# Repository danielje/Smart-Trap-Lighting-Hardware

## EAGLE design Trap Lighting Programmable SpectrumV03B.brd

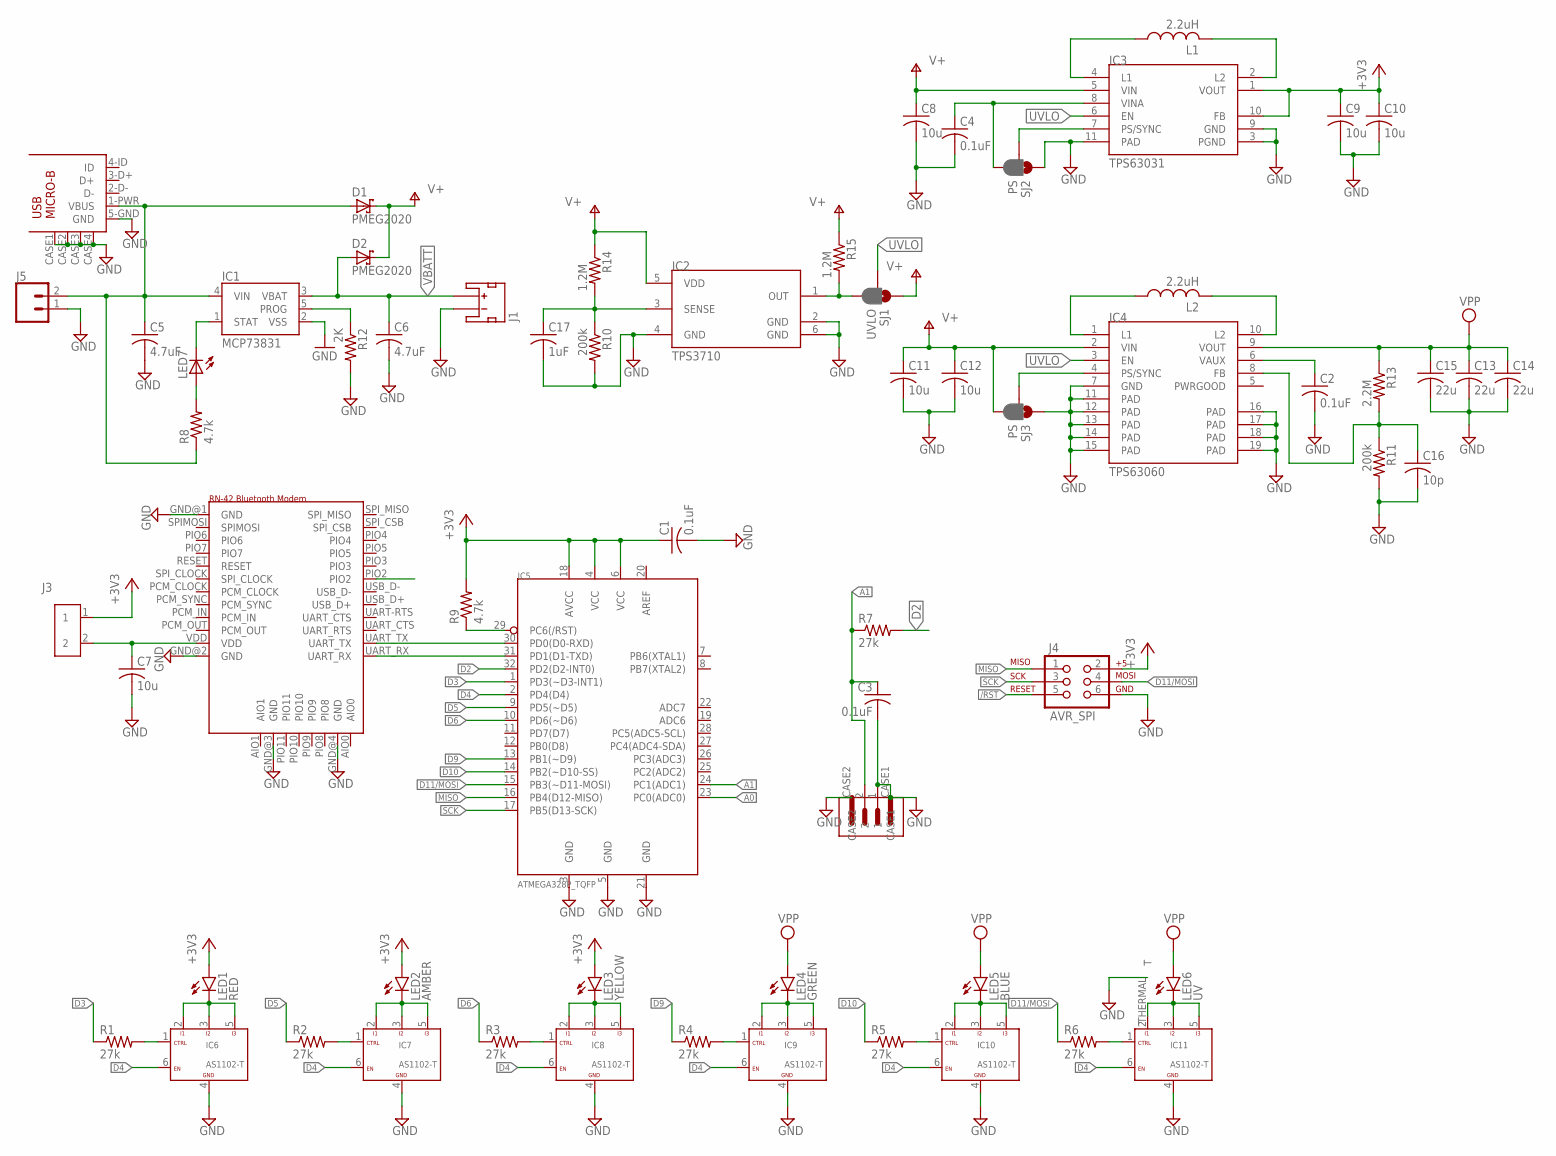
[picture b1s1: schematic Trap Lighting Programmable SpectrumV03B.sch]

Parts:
A1: RN-42_BLUETOOTH; RN-42
C1, C2, C3, C4: 0.1uF; C0805
C5, C6: 4.7uF; C0805
C7, C8, C9, C10, C11, C12: 10u; C0805
C13, C14, C15: 22u; C1206
C16: 10p; C0805
C17: 1uF; C0805
D1, D2: PMEG2020; SOD323_ST
IC1: MCP73831; SOT23-5
IC2: TPS3710; SOT6
IC3: TPS63031; VSON-10
IC4: TPS63060; WSON1-10
IC5: ATMEGA328P_TQFP; TQFP-32
IC6, IC7, IC8, IC9, IC10, IC11: AS1102-T; SC70-6
J1: JST_2MM_MALE; JST-2-SMD
J2: 2PIN_SMD_PHOENIX_CONTACTVERTICAL_PACKAGE; 2-PIN-VERT-PHOENIX_SMD
J3: 2MM_SMD_M_HEADER; 2MM_MALE_SMD_HEADER
J4: AVR_SPI; 2X3
J5: CONN_02PTH3; 1X02_LONGPADS
L1, L2: 2.2uH; VLF302512MT-2R2M-CA_INDUCTOR
LED1: RED; LED_TT_OVS5MX
LED2: AMBER; LED_TT_OVS5MX
LED3: YELLOW; LED_TT_OVS5MX
LED4: GREEN; LED_LUXEON_3535L
LED5: BLUE; LED_TT_OVS5MX
LED6: UV; LED_LITEON_CO3_UV
LED7: LEDCHIPLED_0805; CHIPLED_0805
R1, R2, R3, R4, R5, R6, R7: 27k; R0805
R8, R9: 4.7k; R0805
R10, R11: 200k; R0805
R12: 2K; R0805
R13: 2.2M; R0805
R14, R15: 1.2M; R0805
SJ1: UVLO; SMT-JUMPER_3_1-NC_PASTE_SILK
SJ2, SJ3: PS; SMT-JUMPER_3_1-NC_PASTE_SILK
USB1: USB-MICRO-B; USB_MICRO_B_WURTH_629105136821

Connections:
3.3V: C1.1, C9.1, C10.1, IC3.1 (VOUT), IC3.10 (FB), IC5.4 (VCC), IC5.6 (VCC), IC5.18 (AVCC), J3.1, J4.2, LED1.A, LED2.A, LED3.A, R9.2
/RST: IC5.29 (PC6(/RST)), J4.5, R9.1
A0: IC5.23 (PC0(ADC0))
A1: C3.1, IC5.24 (PC1(ADC1)), J2.2, R7.1
BT_CONNECT: A1.PIO2
D2: IC5.32 (PD2(D2-INT0)), R7.2
D3: IC5.1 (PD3(~D3-INT1)), R1.1
D4: IC5.2 (PD4(D4)), IC6.6 (EN), IC7.6 (EN), IC8.6 (EN), IC9.6 (EN), IC10.6 (EN), IC11.6 (EN)
D5: IC5.9 (PD5(~D5)), R2.1
D6: IC5.10 (PD6(~D6)), R3.1
D9: IC5.13 (PB1(~D9)), R4.1
D10: IC5.14 (PB2(~D10-SS)), R5.1
D11/MOSI: IC5.15 (PB3(~D11-MOSI)), J4.4, R6.1
GND: A1.GND@1 (GND), A1.GND@2 (GND), A1.GND@3 (GND), A1.GND@4 (GND), C1.2, C2.2, C3.2, C4.2, C5.2, C6.2, C7.2, C8.2, C9.2, C10.2, C11.2, C12.2, C13.2, C14.2, C15.2, C16.2, C17.2, IC1.2 (VSS), IC2.2 (GND), IC2.4 (GND), IC2.6 (GND), IC3.3 (PGND), IC3.9 (GND), IC3.11 (PAD), IC4.7 (GND), IC4.11 (PAD), IC4.12 (PAD), IC4.13 (PAD), IC4.14 (PAD), IC4.15 (PAD), IC4.16 (PAD), IC4.17 (PAD), IC4.18 (PAD), IC4.19 (PAD), IC5.3 (GND), IC5.5 (GND), IC5.21 (GND), IC6.4 (GND), IC7.4 (GND), IC8.4 (GND), IC9.4 (GND), IC10.4 (GND), IC11.4 (GND), J1.1 (-), J2.1, J2.CASE1, J2.CASE2, J4.6, J5.1, LED6.THERMAL (T), R10.2, R11.2, R12.2, SJ2.1, SJ3.1, USB1.5-GND (GND), USB1.CASE1 (CASE), USB1.CASE2 (CASE), USB1.CASE3 (CASE), USB1.CASE4 (CASE)
MCURX: A1.UART_TX, IC5.30 (PD0(D0-RXD))
MCUTX: A1.UART_RX, IC5.31 (PD1(D1-TXD))
MISO: IC5.16 (PB4(D12-MISO)), J4.1
unnamed: IC1.1 (STAT), LED7.C
unnamed: IC8.1 (CTRL), R3.2
unnamed: IC9.1 (CTRL), R4.2
unnamed: IC2.1 (OUT), R15.2, SJ1.3
unnamed: A1.VDD, C7.1, J3.2
unnamed: IC10.1 (CTRL), R5.2
unnamed: IC11.1 (CTRL), R6.2
unnamed: IC7.1 (CTRL), R2.2
unnamed: LED7.A, R8.2
unnamed: IC1.5 (PROG), R12.1
unnamed: C17.1, IC2.3 (SENSE), R10.1, R14.2
unnamed: IC3.2 (L2), L1.2
unnamed: IC3.4 (L1), L1.1
unnamed: IC3.7 (PS/SYNC), SJ2.2
unnamed: IC8.2 (I1), IC8.3 (I2), IC8.5 (I3), LED3.C
unnamed: IC9.2 (I1), IC9.3 (I2), IC9.5 (I3), LED4.C
unnamed: IC10.2 (I1), IC10.3 (I2), IC10.5 (I3), LED5.C
unnamed: IC11.2 (I1), IC11.3 (I2), IC11.5 (I3), LED6.K (C)
unnamed: IC7.2 (I1), IC7.3 (I2), IC7.5 (I3), LED2.C
unnamed: IC6.1 (CTRL), R1.2
unnamed: C4.1, IC3.8 (VINA), SJ2.3
unnamed: IC6.2 (I1), IC6.3 (I2), IC6.5 (I3), LED1.C
unnamed: IC4.4 (PS/SYNC), SJ3.2
unnamed: IC4.1 (L1), L2.1
unnamed: IC4.10 (L2), L2.2
unnamed: C2.1, IC4.6 (VAUX)
unnamed: C16.1, IC4.8 (FB), R11.1, R13.2
SCK: IC5.17 (PB5(D13-SCK)), J4.3
USB_VIN: C5.1, D1.A, IC1.4 (VIN), J5.2, R8.1, USB1.1-PWR (VBUS)
UVLO: IC3.6 (EN), IC4.3 (EN), SJ1.2
V+: C8.1, C11.1, C12.1, D1.C, D2.C, IC2.5 (VDD), IC3.5 (VIN), IC4.2 (VIN), R14.1, R15.1, SJ1.1, SJ3.3
VBATT: C6.1, D2.A, IC1.3 (VBAT), J1.2 (+)
VPP: C13.1, C14.1, C15.1, IC4.9 (VOUT), LED4.A, LED5.A, LED6.A, R13.1

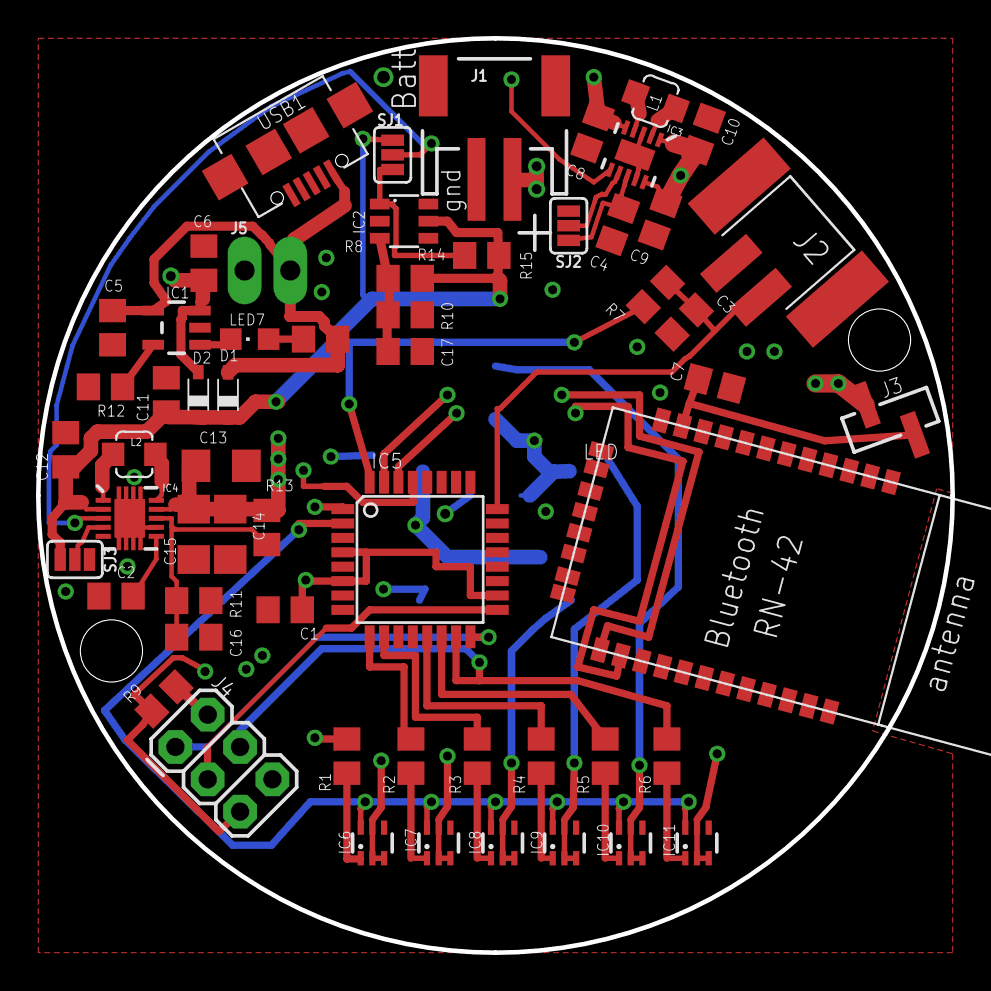
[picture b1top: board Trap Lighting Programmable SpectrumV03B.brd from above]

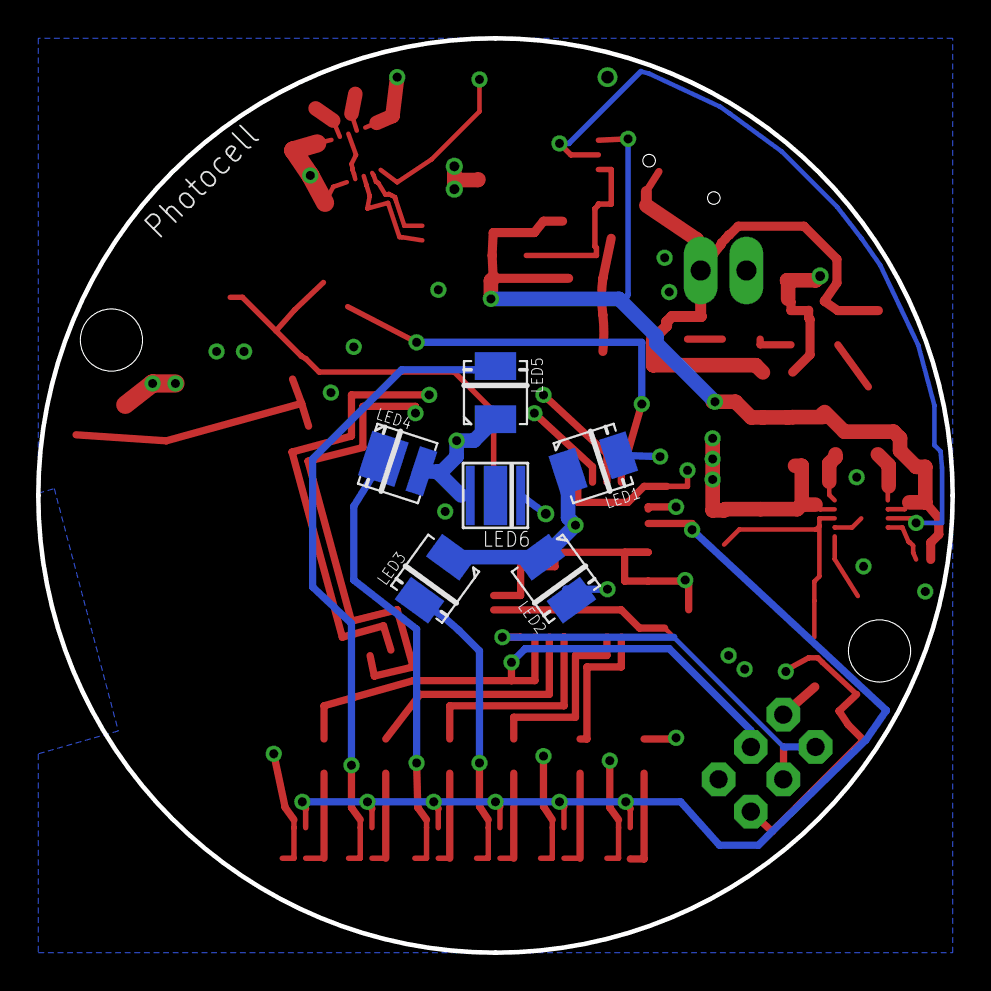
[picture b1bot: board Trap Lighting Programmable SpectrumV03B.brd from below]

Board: 4 copper layers, 50.8 x 50.8 mm, 64 parts (6 on the bottom side), 48 nets.

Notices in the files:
parts and their libraries:
SparkFun-Connectors: Licensing: Creative Commons ShareAlike 4.0 International - https://creativecommons.org/licenses/by-sa/4.0
